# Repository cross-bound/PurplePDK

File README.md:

Purple PDK is a redesign of the [Original FreePDK](https://free-pdk.github.io/) and [easy-pdk-programmer-lite](https://github.com/free-pdk/easy-pdk-programmer-lite-hardware) programmers. It was to challange myself and practice PCB design. It was tested with the Padauk PFS-154. Should work with the all other MCU's that are supported by the original FreePDK programmer.

The board is a 4 layer board with the two inner layers being solid ground planes. The size of the PCB is small enough that it can be ordered unassambled from JLCPCB for $2 (at the time of this writing. With purple solder mask and order number removed it's around $8 for 5 boards).

Changes to the easy-pdk-programmer-lite schematic were made to use a SMD type oscillator. The mircoUSB port was changed to Type-C. Also added was a ESD protection IC which may or may not be needed.

Capacitors, resistors, and LEDs are mostly 0603, plus a few 0805 caps. The pads for 0603 components are slightly extended for hand soldering. But this is definitly not a beginner friendly soldering project.

Dimensions: 52x26mm

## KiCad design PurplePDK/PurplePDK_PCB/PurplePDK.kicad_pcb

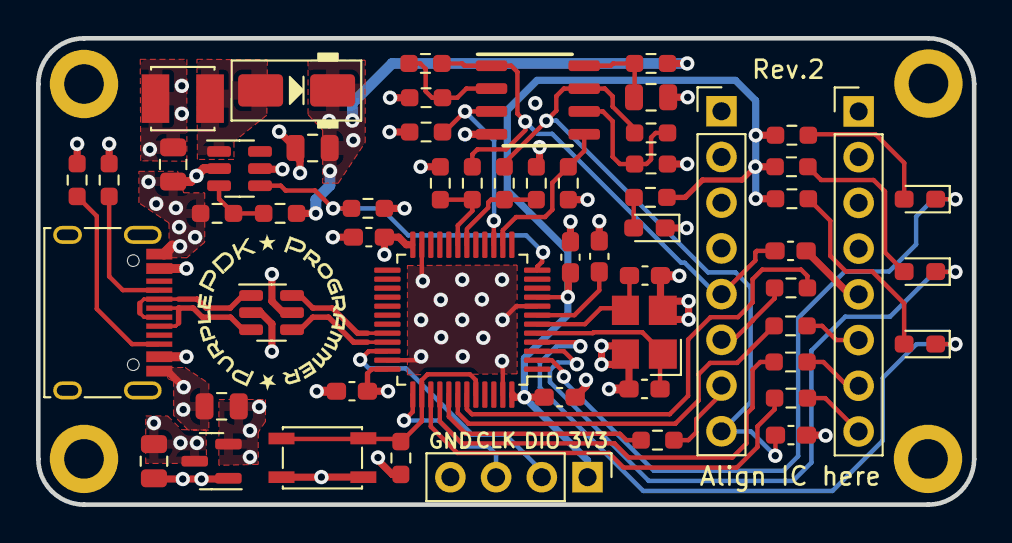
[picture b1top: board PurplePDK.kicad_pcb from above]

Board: 4 copper layers, 52.0 x 25.9 mm, 61 parts (0 on the bottom side), 45 nets.

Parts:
C3, C11, C14, C17, C20: 4u7; C_0805_2012Metric
C5, C7, C8, C9, C10, C15, C16: 100n; C_0603_1608Metric_Pad1.08x0.95mm_HandSolder
C12, C13: 10p; C_0603_1608Metric_Pad1.08x0.95mm_HandSolder
D1-blue1, D2-blue1, D3-yellow1, D4-red1: LED; LED_0603_1608Metric_Pad1.05x0.95mm_HandSolder
D7: SS14; D_SMA
H1, H2, H3, H4: MountingHole_Pad; MountingHole_2.2mm_M2_ISO14580_Pad
J1: USB_C_USB2.0; USB_C_Receptacle_HRO_TYPE-C-31-M-12
J2: SWD; PinHeader_1x04_P2.54mm_Vertical
J3: Header Row 1; PinHeader_1x08_P2.54mm_Vertical
J4: Header Row 2; PinHeader_1x08_P2.54mm_Vertical
L1: 4.7uH; L_Sunlord_SWPA3015S
R1, R16, R17, R18: 1K; R_0603_1608Metric_Pad0.98x0.95mm_HandSolder
R2, R3, R19: 220K; R_0603_1608Metric_Pad0.98x0.95mm_HandSolder
R4: 22; R_0603_1608Metric_Pad0.98x0.95mm_HandSolder
R5, R6, R8, R10, R12, R13: 20K; R_0603_1608Metric_Pad0.98x0.95mm_HandSolder
R7, R11, R22: 100K; R_0603_1608Metric_Pad0.98x0.95mm_HandSolder
R9: 6K2; R_0603_1608Metric_Pad0.98x0.95mm_HandSolder
R14, R15: 5K1; R_0603_1608Metric_Pad0.98x0.95mm_HandSolder
R20, R21, R25, R26, R27: 100; R_0603_1608Metric_Pad0.98x0.95mm_HandSolder
R23: 3K9; R_0603_1608Metric_Pad0.98x0.95mm_HandSolder
SW1: SW_Push; SW_SPST_PTS810
U1: AS358AM; SO-8_3.9x4.9mm_P1.27mm
U2: USBLC6-2SC6; SOT-23-6
U3: STM32F072C8T6; LQFP-48_7x7mm_P0.5mm
U4: XC6206P332MR; SOT-23
U5: MT3608; SOT-23-6
Y1: 8Mhz; Oscillator_SMD_Abracon_ASE-4Pin_3.2x2.5mm_HandSoldering

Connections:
+3V3: C7.1, C8.1, C9.1, C10.1, C14.1, J2.1, R1.1, R16.1, R17.1, R18.1, SW1.1, U3.9 (VDDA), U3.24 (VDD), U3.36 (VDDIO2), U3.48 (VDD), U4.2 (VO)
+15V: C20.1, D7.1 (K), R4.1, R22.2
/CC1: J1.A5 (CC1), R14.2
/CC2: J1.B5 (CC2), R15.2
/CONN_USB+: J1.A6 (D+), J1.B6 (D+), U2.3 (I/O2)
/CONN_USB-: J1.A7 (D-), J1.B7 (D-), U2.1 (I/O1)
/HSE_IN: C12.1, U3.5 (PF0), Y1.1
/HSE_OUT: C13.1, U3.6 (PF1), Y1.3
/ICPCK_H: J4.8, R27.1
/ICPDA_H: J3.7, R21.1
/NRST: C5.1, U3.7 (NRST)
/PB4_H: J4.7, R26.1
/PB6_H: J4.6, R25.1
/PB7_H: J3.6, R20.1
BOOT0_CONN: R13.2, SW1.2, U3.38 (PA15), U3.44 (BOOT0)
GND: C3.2, C5.2, C7.2, C8.2, C9.2, C10.2, C11.2, C12.2, C13.2, C14.2, C15.2, C16.2, C17.2, C20.2, D1-blue1.1 (K), H1.1, H2.1, H3.1, H4.1, J1.A1 (GND), J1.A12 (GND), J1.B1 (GND), J1.B12 (GND), J2.4, J4.5, R2.2, R3.2, R6.1, R8.2, R9.1, R12.2, R13.1, R14.1, R15.1, R19.1, R23.2, U1.4 (V-), U2.2 (GND), U3.8 (VSSA), U3.23 (VSS), U3.35 (VSS), U3.47 (VSS), U4.1 (GND), U5.2 (GND), Y1.2, Y1.4
ICPCK: R27.2, U3.39 (PB3)
ICPDA: R21.2, U3.41 (PB5)
ICVDD: C16.1, J3.5, R5.1, R7.2, U1.1
ICVPP: C15.1, J3.8, R10.1, R11.2, U1.7
unnamed: D1-blue1.2 (A), R1.2
unnamed: D2-blue1.2 (A), R16.2
unnamed: D2-blue1.1 (K), U3.2 (PC13)
unnamed: D3-yellow1.2 (A), R17.2
unnamed: D3-yellow1.1 (K), U3.3 (PC14)
unnamed: D4-red1.2 (A), R18.2
unnamed: D4-red1.1 (K), U3.4 (PC15)
unnamed: D7.2 (A), L1.2, U5.1 (SW)
unnamed: R5.2, R6.2, U1.2 (-)
unnamed: C3.1, R4.2, U1.8 (V+)
unnamed: R9.2, R10.2, U1.6 (-)
unnamed: R22.1, R23.1, U5.3 (FB)
PA2: R19.2, U3.12 (PA2), U5.4 (EN)
PA4_OP: R2.1, U1.5 (+), U3.14 (PA4)
PA5_OP: R3.1, U1.3 (+), U3.15 (PA5)
PB0_OP: R11.1, R12.1, U3.18 (PB0)
PB1_OP: R7.1, R8.1, U3.19 (PB1)
PB4: R26.2, U3.40 (PB4)
PB6: R25.2, U3.42 (PB6)
PB7: R20.2, U3.43 (PB7)
SWCLK: J2.3, U3.37 (PA14)
SWDIO: J2.2, U3.34 (PA13)
USB_D+: U2.4 (I/O2), U3.33 (PA12)
USB_D-: U2.6 (I/O1), U3.32 (PA11)
VBUS: C11.1, C17.1, J1.A4 (VBUS), J1.A9 (VBUS), J1.B4 (VBUS), J1.B9 (VBUS), L1.1, U2.5 (VBUS), U4.3 (VI), U5.5 (IN)
